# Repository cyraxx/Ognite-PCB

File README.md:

# Overview

The [Ognite Flameless Digital Candle](http://ognite.com/) is an original project by Josh Levin. It displays a realistic flame animation on its LED matrix and is also an exercise in minimalism: The only components are an AVR microcontroller, 40 LEDs, and a rather ingenious laser-cut cardboard construction that not only acts as the box that the components come in but also holds the assembled circuit and batteries in place.

Unfortunately, the project seems to be dead and I do not have access to a laser cutter either so I decided to make a PCB. And since I was breaking with the minimalism theme anyway I also added an on/off switch.

The `.sch` and `.brd` files are in [EAGLE 7](http://www.cadsoftusa.com/download-eagle/eagle-freeware/) format and compatible with the freeware version.

# Bill of materials

| Qty | Component | Notes | Farnell item# |
| --- | --- | --- | --- |
| 1 | Ognite Clone PCB | Can be ordered at [Dirty PCBs](http://dirtypcbs.com/view.php?share=20653&accesskey=263dad38d5838c2409e7b28eb41107fe) |
| 40 | 3mm Amber LED | A lot of brightness is lost due to the matrix switching so go with some super bright ones! | 1581166 |
| 1 | ATtiny4313-PU | With [Ognite firmware](https://github.com/cyraxx/ognite-firmware/) | 1841620 |
| 1 | DIP-20 socket | Technically optional if you are very certain that you will never have to re-flash the chip... | 1103848 |
| 1 | 3x AAA battery box | | 1650688 |
| 1 | SPDT slide switch | Pretty much any model with ~4.6-4.8 mm pin distance should fit | 807527 |

# Assembly notes

The flat side of the LED outline on the silkscreen denotes the cathode, i.e. the shorter lead.

The switch is meant to be mounted on the back of the PCB but since it's symmetrical it can also go on the front.

The assembled PCB can be mounted on top of the battery box with some hot glue like so:

# Gerber files

Gerber files created to [Dirty PCBs](http://dirtypcbs.com/) specifications are included in the `gerbers` directory. If you create your own Gerber or other export from EAGLE it is recommended that you include the `tDocu` layer in the silkscreen as it contains the LED orientation.

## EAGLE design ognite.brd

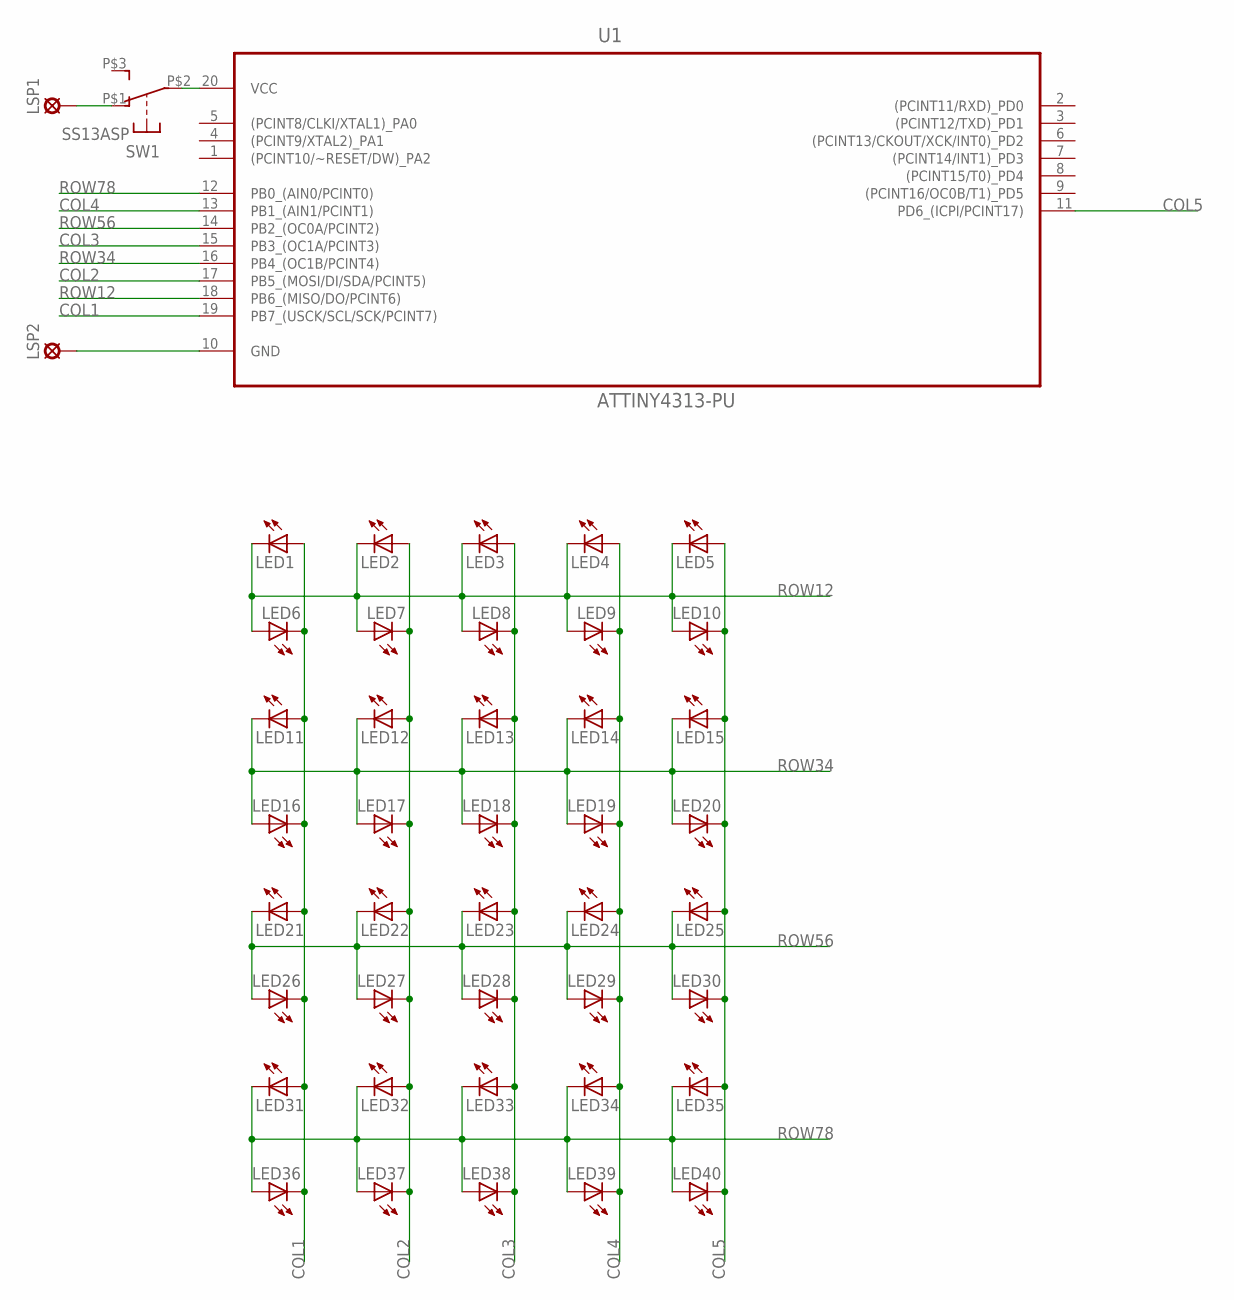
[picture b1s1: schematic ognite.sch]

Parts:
LED1, LED2, LED3, LED4, LED5, LED6, LED7, LED8, LED9, LED10, LED11, LED12, LED13, LED14, LED15, LED16, LED17, LED18, LED19, LED20, LED21, LED22, LED23, LED24, LED25, LED26, LED27, LED28, LED29, LED30, LED31, LED32, LED33, LED34, LED35, LED36, LED37, LED38, LED39, LED40: LED3MM
LSP1, LSP2: SE14
SW1: SS13ASP; T80-S
U1: ATTINY4313-PU; DIP254P762X533-20

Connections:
COL1: LED1.A, LED6.K (C), LED11.A, LED16.K (C), LED21.A, LED26.K (C), LED31.A, LED36.K (C), U1.19 (PB7_(USCK/SCL/SCK/PCINT7))
COL2: LED2.A, LED7.K (C), LED12.A, LED17.K (C), LED22.A, LED27.K (C), LED32.A, LED37.K (C), U1.17 (PB5_(MOSI/DI/SDA/PCINT5))
COL3: LED3.A, LED8.K (C), LED13.A, LED18.K (C), LED23.A, LED28.K (C), LED33.A, LED38.K (C), U1.15 (PB3_(OC1A/PCINT3))
COL4: LED4.A, LED9.K (C), LED14.A, LED19.K (C), LED24.A, LED29.K (C), LED34.A, LED39.K (C), U1.13 (PB1_(AIN1/PCINT1))
COL5: LED5.A, LED10.K (C), LED15.A, LED20.K (C), LED25.A, LED30.K (C), LED35.A, LED40.K (C), U1.11 (PD6_(ICPI/PCINT17))
GND: LSP2.MP, U1.10 (GND)
unnamed: SW1.P$2 (COM), U1.20 (VCC)
unnamed: LSP1.MP, SW1.P$1 (S1)
ROW12: LED1.K (C), LED2.K (C), LED3.K (C), LED4.K (C), LED5.K (C), LED6.A, LED7.A, LED8.A, LED9.A, LED10.A, U1.18 (PB6_(MISO/DO/PCINT6))
ROW34: LED11.K (C), LED12.K (C), LED13.K (C), LED14.K (C), LED15.K (C), LED16.A, LED17.A, LED18.A, LED19.A, LED20.A, U1.16 (PB4_(OC1B/PCINT4))
ROW56: LED21.K (C), LED22.K (C), LED23.K (C), LED24.K (C), LED25.K (C), LED26.A, LED27.A, LED28.A, LED29.A, LED30.A, U1.14 (PB2_(OC0A/PCINT2))
ROW78: LED31.K (C), LED32.K (C), LED33.K (C), LED34.K (C), LED35.K (C), LED36.A, LED37.A, LED38.A, LED39.A, LED40.A, U1.12 (PB0_(AIN0/PCINT0))

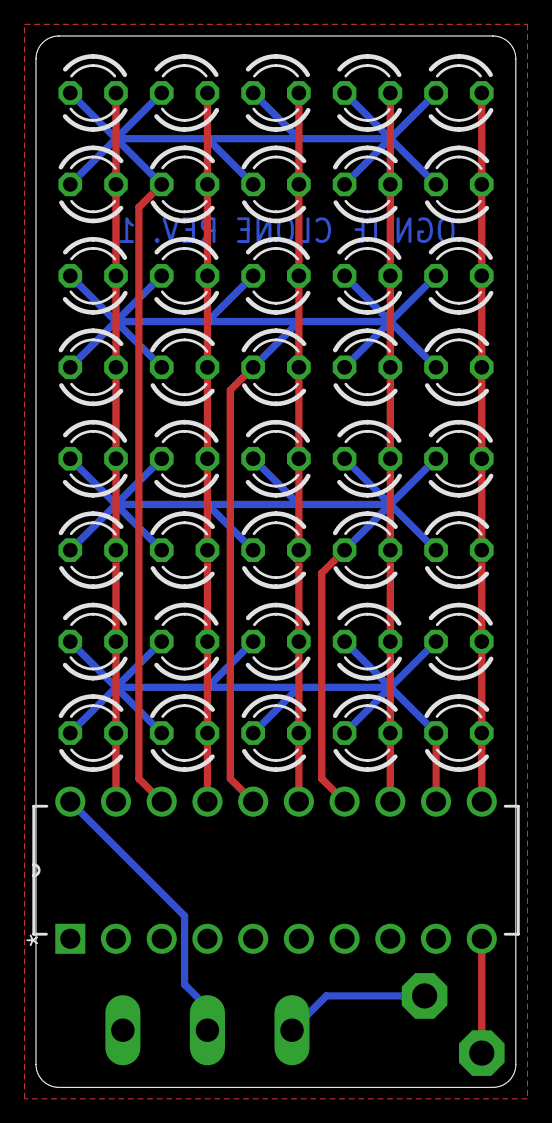
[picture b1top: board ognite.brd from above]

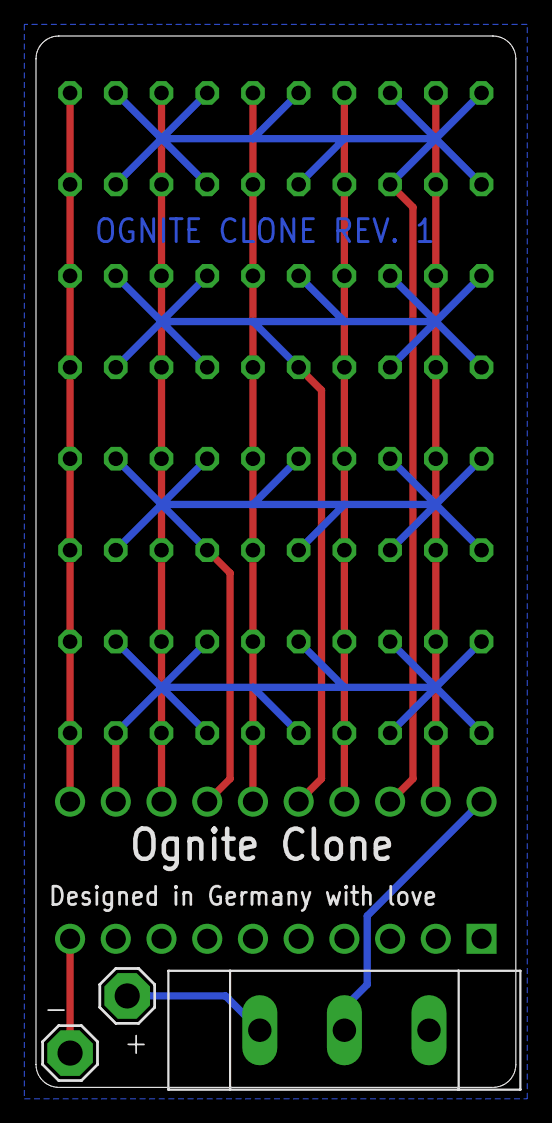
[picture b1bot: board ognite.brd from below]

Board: 2 copper layers, 26.7 x 58.4 mm, 44 parts (3 on the bottom side), 12 nets.

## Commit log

2016-07-19 Added PDFs
2016-07-19 README tweaks
